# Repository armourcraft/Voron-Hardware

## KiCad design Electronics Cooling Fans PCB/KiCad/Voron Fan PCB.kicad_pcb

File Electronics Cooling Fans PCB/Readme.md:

# Electronics Bay Cooling Fans PCB

Designed by ArmourCraft
PCB to combine cooling fans to avoid splicing, making replacement easier.

!(Images/PCB_loose.png)
!(Images/PCB_installed.png)

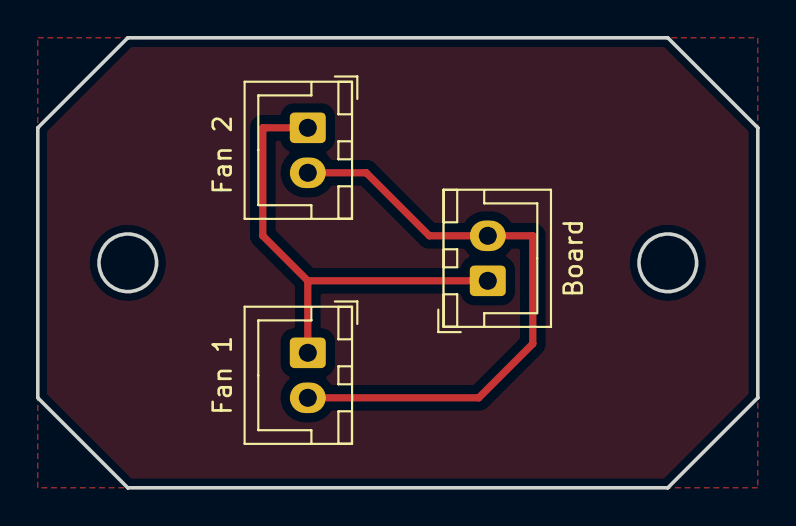
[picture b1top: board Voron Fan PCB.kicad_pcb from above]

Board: 2 copper layers, 40.0 x 25.0 mm, 3 parts (0 on the bottom side), 2 nets.

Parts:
Board: J3; JST_XH_B2B-XH-A_1x02_P2.50mm_Vertical
Fan 1: J1; JST_XH_B2B-XH-A_1x02_P2.50mm_Vertical
Fan 2: J2; JST_XH_B2B-XH-A_1x02_P2.50mm_Vertical

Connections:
unnamed: Board.1, Fan 1.1, Fan 2.1
unnamed: Board.2, Fan 1.2, Fan 2.2

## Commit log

2023-02-08 Upload
